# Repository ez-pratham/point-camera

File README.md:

# POINT CAMERA

**POINT CAMERA** is an open-source, minimalist point-and-shoot camera inspired by bare-PCB, transparent retro cameras. Engineered around the dual-core **ESP32** microcontroller, it features a 24-pin DVP CMOS image sensor, a high-contrast 0.96" OLED live HUD, a high-speed SPI MicroSD card slot, an ergonomic shoulder shutter button, a 4-way tactile D-Pad for real-time retro film filters, and innovative integrated side-wall slider grooves that allow a glass or acrylic viewfinder sheet to slide directly into the PCB!

When the **MODE** button is pressed, the camera cycles between 4 distinct photographic color profiles: **Natural (Normal)**, **Vivid Retro Warm**, **Monochrome B&W**, and **1970s Vintage Sepia**.

---

## Photos & Screenshots

### Isometric 3D View (Full Assembly)

### Top View (Silkscreen Pin Labels & Controls)

### Bottom View (Solid Ground Plane & Interconnects)

---

## How It Works

### How the parts fit on the camera

Every section of the carrier board is ergonomically laid out so that the bare PCB can be used directly as a standalone point-and-shoot camera without needing any 3D-printed enclosure:

1. **Center Viewfinder (Optical Aperture & Slider Grooves)**:
   - A $42.0 \times 34.0\text{ mm}$ clear rectangular optical aperture is centered on the PCB.
   - Recessed vertical guide channels (`GROOVE-L` at $X = 38.5\text{ mm}$ and `GROOVE-R` at $X = 87.5\text{ mm}$) are routed directly into the inner side walls of the PCB.
   - Solid $3.5\text{ mm}$ horizontal bottom stop shelves at $Y = 31.0\text{ mm}$ hold a clear glass or acrylic viewfinder sheet in place, sliding in directly from the top edge.

2. **Left Wing Core (Microcontroller & Power Bay)**:
   - An **ESP32 36-Pin Development Board (NodeMCU-32S / ESP-WROOM-32)** is mounted into female socket headers (`J_ESP_TOP` and `J_ESP_BOT`) with zero desoldering.
   - The ESP32's onboard USB-C / Micro-USB connector faces downwards at the bottom edge, allowing direct plug-in power from any portable 5V USB power bank.

3. **Top Shoulder (Ergonomic Shutter Button)**:
   - A tactile push button switch (`SW2`) is positioned at the top-left shoulder of the board ($X = 14.0\text{ mm}$, $Y = 7.0\text{ mm}$).
   - It connects directly between `GPIO 18` and ground using the ESP32's internal `INPUT_PULLUP` (zero external resistors!).

4. **Right Wing (Inverted OLED HUD & Storage Bay)**:
   - **Inverted 0.96" SSD1306 I2C OLED (`DISP1`)**: Mounted upside down with the display glass extending outward towards $Y = 0.0\text{ mm}$ to eliminate physical collisions with the adjacent SD module. Rendered right-side up in firmware via `display.setRotation(2);`.
   - **Reusable SPI MicroSD Module (`J4`)**: Plugs into a 6-pin female socket (`[CS, SCK, MOSI, MISO, 3.3V, GND]`) for tool-free MicroSD card swapping and photo saving under `/DCIM/IMG_xxxx.JPG`.

5. **Center Bottom (24-Pin DVP Camera Sensor)**:
   - A high-density **Hirose FH12-24S-0.5SH bottom-contact FPC connector (`CAM1`)** drives an **OV2640 (2 MP)** or **OV5640 (5 MP)** image sensor ribbon cable.

6. **Right Bottom (4-Way Navigation D-Pad)**:
   - A cluster of tactile buttons (`SW3` UP, `SW4` DOWN, `SW5` LEFT, `SW6` RIGHT) lets you cycle color profiles, adjust exposure compensation (EV), and open the photo playback gallery.

---

## Bill of Materials (BOM)

| Item | Qty | Supplier | Cost/item | Total Cost | link |
| :--- | :---: | :--- | :---: | :---: | :--- |
| **ESP32 38-Pin Development Board (Dual-Core WiFi/BT)** | 1 | Robu.in | $5.35 | $5.35 | [Robu.in](https://robu.in/product/esp32-38pin-development-board-wifibluetooth-ultra-low-power-consumption-dual-core/) |
| **0.96-inch I2C OLED Display Module (SSD1306 128x64 Blue)** | 1 | Robu.in | $2.15 | $2.15 | [Robu.in](https://robu.in/product/0-96-inch-i2c-oled-display-module-blue/) |
| **Micro SD Card Adapter Module (SPI Interface)** | 1 | Robu.in | $0.75 | $0.75 | [Robu.in](https://robu.in/product/micro-sd-card-module/) |
| **OV2640 2MP Camera Module with 24-Pin FPC Cable** | 1 | Robu.in | $4.85 | $4.85 | [Robu.in](https://robu.in/product/ov2640-camera-module-with-adapter-board/) |
| **SanDisk Ultra 16GB MicroSDHC UHS-I Card (Class 10)** | 1 | Robu.in | $3.90 | $3.90 | [Robu.in](https://robu.in/product/sandisk-ultra-16gb-microsdhc-uhs-i-card/) |
| **6x6x5mm Tactile Push Button Switches (Pack of 10)** | 1 | Robu.in | $0.23 | $0.23 | [Robu.in](https://robu.in/product/6x6x5-tactile-push-button-switch/) |
| **Hirose 24-Pin 0.5mm Pitch Bottom-Contact FPC Connector** | 1 | LCSC | $0.45 | $0.45 | [LCSC](https://www.lcsc.com/product-detail/FFC-FPC-Connectors_Hirose-Electric-FH12-24S-0-5SH-55_C23912.html) |
| **2.54mm 1x40-Pin Female Single Row Header Strips (Pack of 10)** | 1 | Robu.in | $1.43 | $1.43 | [Robu.in](https://robu.in/product/2-54mm-1x40-pin-female-single-row-header-strip-pack-of-10/) |
| **M2.5 Brass Hex Threaded Pillar Standoff Spacers (Pack of 10)** | 1 | Robu.in | $0.95 | $0.95 | [Robu.in](https://robu.in/product/m2-5-brass-hex-threaded-pillar-standoff-spacers-pack-of-10/) |
| **Importing Tax and Customs Duty** | 1 | Customs / Shipping | $35.00 | $35.00 | — |
| **Estimated total shipping** | 1 | — | — | $0.00 | — |
| **Total Project Cost** | **9** | — | — | **$55.06** | — |

*Downloadable spreadsheet format is available at [BOM.csv](BOM.csv).*

---

## How to Build

1. **Solder the Low-Profile Surface Mount FPC Connector**:
   - Align the 24-pin 0.5mm pitch `CAM1` connector onto the SMD pads at the bottom center of the board.
   - Solder using a fine-tip soldering iron or solder paste and hot air.
2. **Solder the Tactile Push Buttons**:
   - Insert and solder the 5× 6×6×5mm tactile buttons: `SW2` (Shutter), `SW3` (UP), `SW4` (DOWN), `SW5` (LEFT), and `SW6` (RIGHT).
3. **Solder the Female Socket Headers**:
   - Solder the 2× 1×18 female socket headers for the ESP32 (`J_ESP_TOP` and `J_ESP_BOT`).
   - Solder the 1×4 female socket header for the OLED display (`DISP1`).
   - Solder the 1×6 female socket header for the MicroSD module (`J4`).
4. **Mount the M2.5 Brass Standoffs**:
   - Fasten the 6× M2.5 brass standoffs through mounting holes `H1` to `H6` to protect the PCB back and give it a firm grip.
5. **Slide in the Viewfinder Sheet**:
   - Slide the clear acrylic or glass sheet ($48.5 \times 32 \times 1.5\text{ mm}$) into the left and right side-wall grooves (`GROOVE-L` and `GROOVE-R`) until it rests on the bottom stop shelves.
6. **Plug In the Modular Breakout Boards**:
   - Insert the ESP32 board into `J_ESP_TOP` and `J_ESP_BOT`.
   - Plug the 0.96" SSD1306 OLED into `DISP1` (glass facing downward).
   - Plug the SPI MicroSD card module into `J4`.
   - Insert the 24-pin FPC camera ribbon into `CAM1` and lock the flip latch.
7. **Connect USB Power & Shoot**:
   - Plug any standard 5V USB power bank into the ESP32 USB port. Aim through the optical viewfinder and press the Shutter button!

---

## Software

The firmware supports physical hardware, the Wokwi online web simulator, and live laptop webcam streaming via serial bridge.

### Arduino IDE Upload Instructions
1. Open the Arduino IDE (v2.0 or newer).
2. In **File > Preferences > Additional Boards Manager URLs**, add:
   ```
   https://raw.githubusercontent.com/espressif/arduino-esp32/gh-pages/package_esp32_index.json
   ```
3. In **Tools > Board > Boards Manager**, install `esp32` by Espressif.
4. In **Sketch > Include Library > Manage Libraries...**, install:
   - `Adafruit SSD1306`
   - `Adafruit GFX Library`
5. Under **Tools**, configure:
   - **Board**: `ESP32 Dev Module`
   - **Partition Scheme**: `Huge APP (3MB No OTA/1MB SPIFFS)`
   - **CPU Frequency**: `240MHz`
6. Open the firmware sketch: [`esp32_camera_firmware.ino`](esp32_camera_firmware.ino).
7. Select your COM port and hit **Upload**!

---

## 💻 Wokwi Browser Simulation

Test the entire camera circuit directly in your web browser using **[Wokwi](https://wokwi.com)**:
- Full wiring diagram connecting the ESP32 MCU, 0.96" SSD1306 OLED, SPI MicroSD card, and 5 tactile push buttons.
- Test shutter clicks, live HUD updates, filter switching, and virtual SD card JPEG saving.
- Check out the **[`wokwi/` directory](wokwi/README.md)** for 3-step launch instructions!

---

## KiCad & Production Files

All hardware design files are verified with KiCad 10.0 and have achieved a verified **0 DRC violation, 0 unconnected item** score:

- **KiCad PCB Layout**: [diy_camera.kicad_pcb](diy_camera.kicad_pcb)
- **Fabrication Gerber Archive**: [gerbers/](gerbers/) *(RS-274X Gerbers & Excellon drill files)*
- **Bill of Materials Spreadsheet**: [BOM.csv](BOM.csv)
- **Bill of Materials Documentation**: [BOM.md](BOM.md)
- **KiCad DRC Verification Report**: [diy_camera-drc.rpt](diy_camera-drc.rpt) *(0 errors)*

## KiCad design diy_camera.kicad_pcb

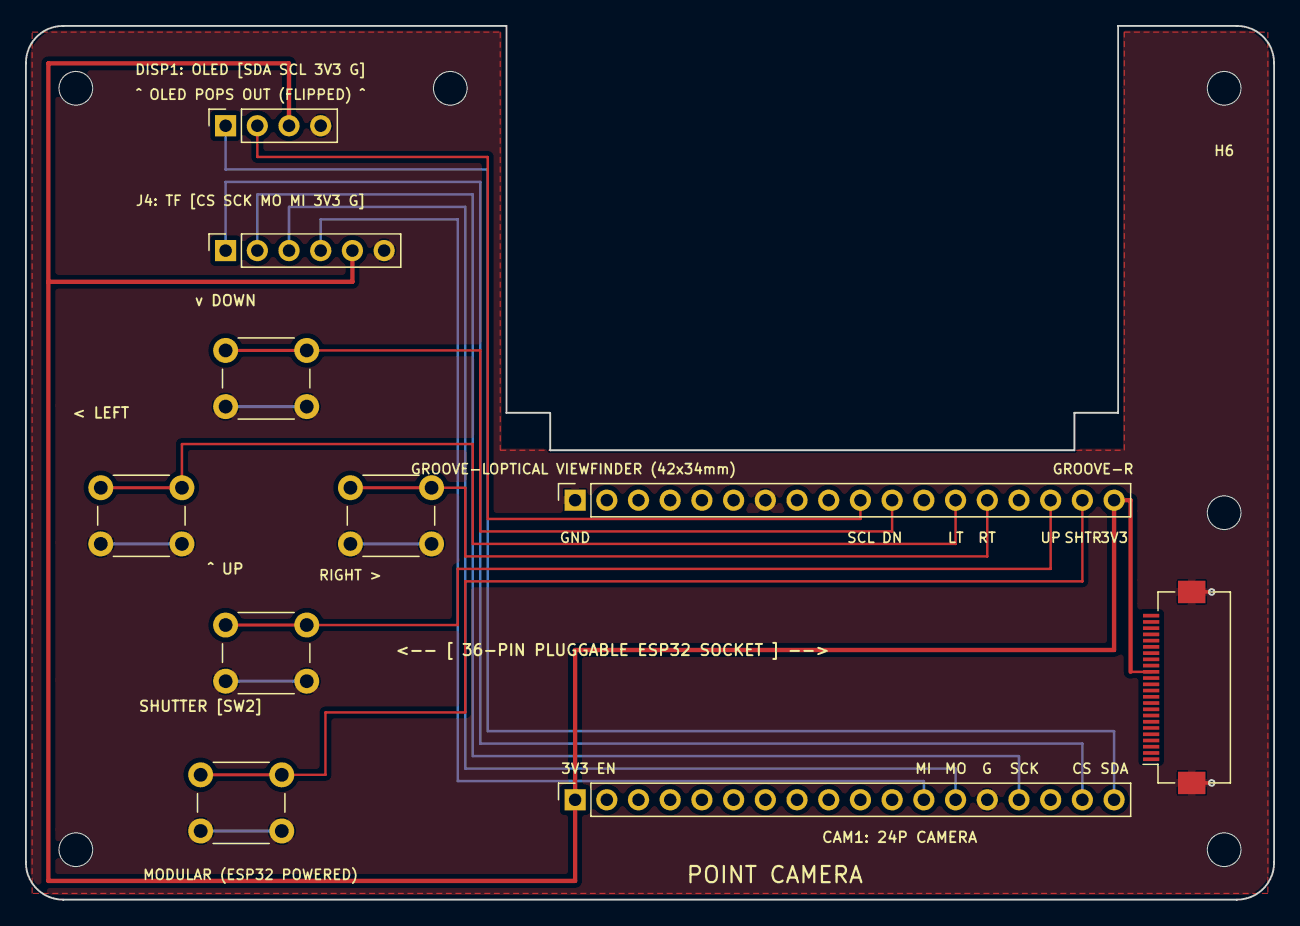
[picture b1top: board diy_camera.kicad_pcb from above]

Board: 2 copper layers, 100.0 x 70.0 mm, 16 parts (0 on the bottom side), 13 nets.

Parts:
CAM1: FPC_24P_0.5mm; Hirose_FH12-24S-0.5SH_1x24-1MP_P0.50mm_Horizontal
DISP1: OLED_SOCKET; PinSocket_1x04_P2.54mm_Vertical
H1, H2, H3, H4, H5, H6: M2.5; MountingHole_2.7mm_M2.5
J4: SD_MODULE_SOCKET; PinSocket_1x06_P2.54mm_Vertical
J_ESP_BOT: ESP32_BOT; PinSocket_1x18_P2.54mm_Vertical
J_ESP_TOP: ESP32_TOP; PinSocket_1x18_P2.54mm_Vertical
SW2: SHUTTER; SW_PUSH_6mm_H5mm
SW3: BTN_UP; SW_PUSH_6mm_H5mm
SW4: BTN_DOWN; SW_PUSH_6mm_H5mm
SW5: BTN_LEFT; SW_PUSH_6mm_H5mm
SW6: BTN_RIGHT; SW_PUSH_6mm_H5mm

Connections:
+3V3: CAM1.15, DISP1.3, J4.5, J_ESP_BOT.18, J_ESP_TOP.1
BTN_DOWN: J_ESP_BOT.11, SW4.1
BTN_LEFT: J_ESP_BOT.13, SW5.1
BTN_RIGHT: J_ESP_BOT.14, SW6.1
BTN_SHUTTER: J_ESP_BOT.17, SW2.1
BTN_UP: J_ESP_BOT.16, SW3.1
GND: CAM1.MP, DISP1.4, J4.6, J_ESP_BOT.1, J_ESP_BOT.7, J_ESP_TOP.14, SW2.2, SW3.2, SW4.2, SW5.2, SW6.2
I2C_SCL: DISP1.2, J_ESP_BOT.10
I2C_SDA: DISP1.1, J_ESP_TOP.18
SD_CS: J4.1, J_ESP_TOP.17
SD_MISO: J4.4, J_ESP_TOP.12
SD_MOSI: J4.3, J_ESP_TOP.13
SD_SCK: J4.2, J_ESP_TOP.15

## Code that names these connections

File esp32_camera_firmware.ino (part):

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// ==========================================

// I2C OLED Display (0.96" 128x64 SSD1306 via DISP1 Socket)
#define I2C_SDA_PIN       21   // J_ESP_TOP Pin 18 (GPIO 21 / SDA)
#define I2C_SCL_PIN       22   // J_ESP_BOT Pin 10 (GPIO 22 / SCL)
#define OLED_RESET_PIN    -1
#define SCREEN_WIDTH      128
#define SCREEN_HEIGHT     64
#define OLED_I2C_ADDR     0x3C

// Tactile Push Buttons (Active LOW with internal INPUT_PULLUP, zero external resistors)
#define PIN_BTN_SHUTTER   18   // SW2 (Top Shoulder) -> J_ESP_BOT Pin 17 (GPIO 18)
#define PIN_BTN_UP        15   // SW3 (D-Pad UP)     -> J_ESP_BOT Pin 16 (GPIO 15)
#define PIN_BTN_RIGHT     2    // SW6 (D-Pad RIGHT)  -> J_ESP_BOT Pin 14 (GPIO 2)
#define PIN_BTN_LEFT      4    // SW5 (D-Pad LEFT)   -> J_ESP_BOT Pin 13 (GPIO 4)
#define PIN_BTN_DOWN      17   // SW4 (D-Pad DOWN)   -> J_ESP_BOT Pin 11 (GPIO 17)

// MicroSD Card SPI Interface (J4 Socket to J_ESP_TOP)
#define PIN_SD_MISO       14   // J4.4 (MISO) -> J_ESP_TOP Pin 12 (GPIO 14)
#define PIN_SD_MOSI       12   // J4.3 (MOSI) -> J_ESP_TOP Pin 13 (GPIO 12)
#define PIN_SD_SCK        13   // J4.2 (SCK)  -> J_ESP_TOP Pin 15 (GPIO 13)
#define PIN_SD_CS         10   // J4.1 (CS)   -> J_ESP_TOP Pin 17 (GPIO 10)

// DVP Camera Interface Pins (OV5640 / OV2640 24-Pin)
#define PWDN_GPIO_NUM     -1
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// ==========================================

void init_gpio() {
  pinMode(PIN_BTN_SHUTTER, INPUT_PULLUP);
  pinMode(PIN_BTN_UP,      INPUT_PULLUP);
  pinMode(PIN_BTN_DOWN,    INPUT_PULLUP);
  pinMode(PIN_BTN_LEFT,    INPUT_PULLUP);
  pinMode(PIN_BTN_RIGHT,   INPUT_PULLUP);
}

void init_oled() {
  Wire.begin(I2C_SDA_PIN, I2C_SCL_PIN);
  if (!display.begin(SSD1306_SWITCHCAPVCC, OLED_I2C_ADDR)) {
    Serial.println("[ERROR] SSD1306 allocation failed");
    return;
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}

void init_sd() {
  SPI.begin(PIN_SD_SCK, PIN_SD_MISO, PIN_SD_MOSI, PIN_SD_CS);
  if (!SD.begin(PIN_SD_CS)) {
    Serial.println("[WARN] Card Mount Failed, retrying...");
    sd_card_mounted = false;
  } else {
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  unsigned long now = millis();

  // 1. Shutter Button Trigger (SW2 / GPIO 18)
  if (digitalRead(PIN_BTN_SHUTTER) == LOW) {
    if (now - last_shutter_time > DEBOUNCE_MS) {
      last_shutter_time = now;
      capture_photo();
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  }

  // 2. D-Pad Mode Switching (RIGHT button cycles color profiles)
  if (digitalRead(PIN_BTN_RIGHT) == LOW) {
    if (now - last_shutter_time > DEBOUNCE_MS) {
      last_shutter_time = now;
      current_mode = (CameraMode)((current_mode + 1) % MODE_COUNT);
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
